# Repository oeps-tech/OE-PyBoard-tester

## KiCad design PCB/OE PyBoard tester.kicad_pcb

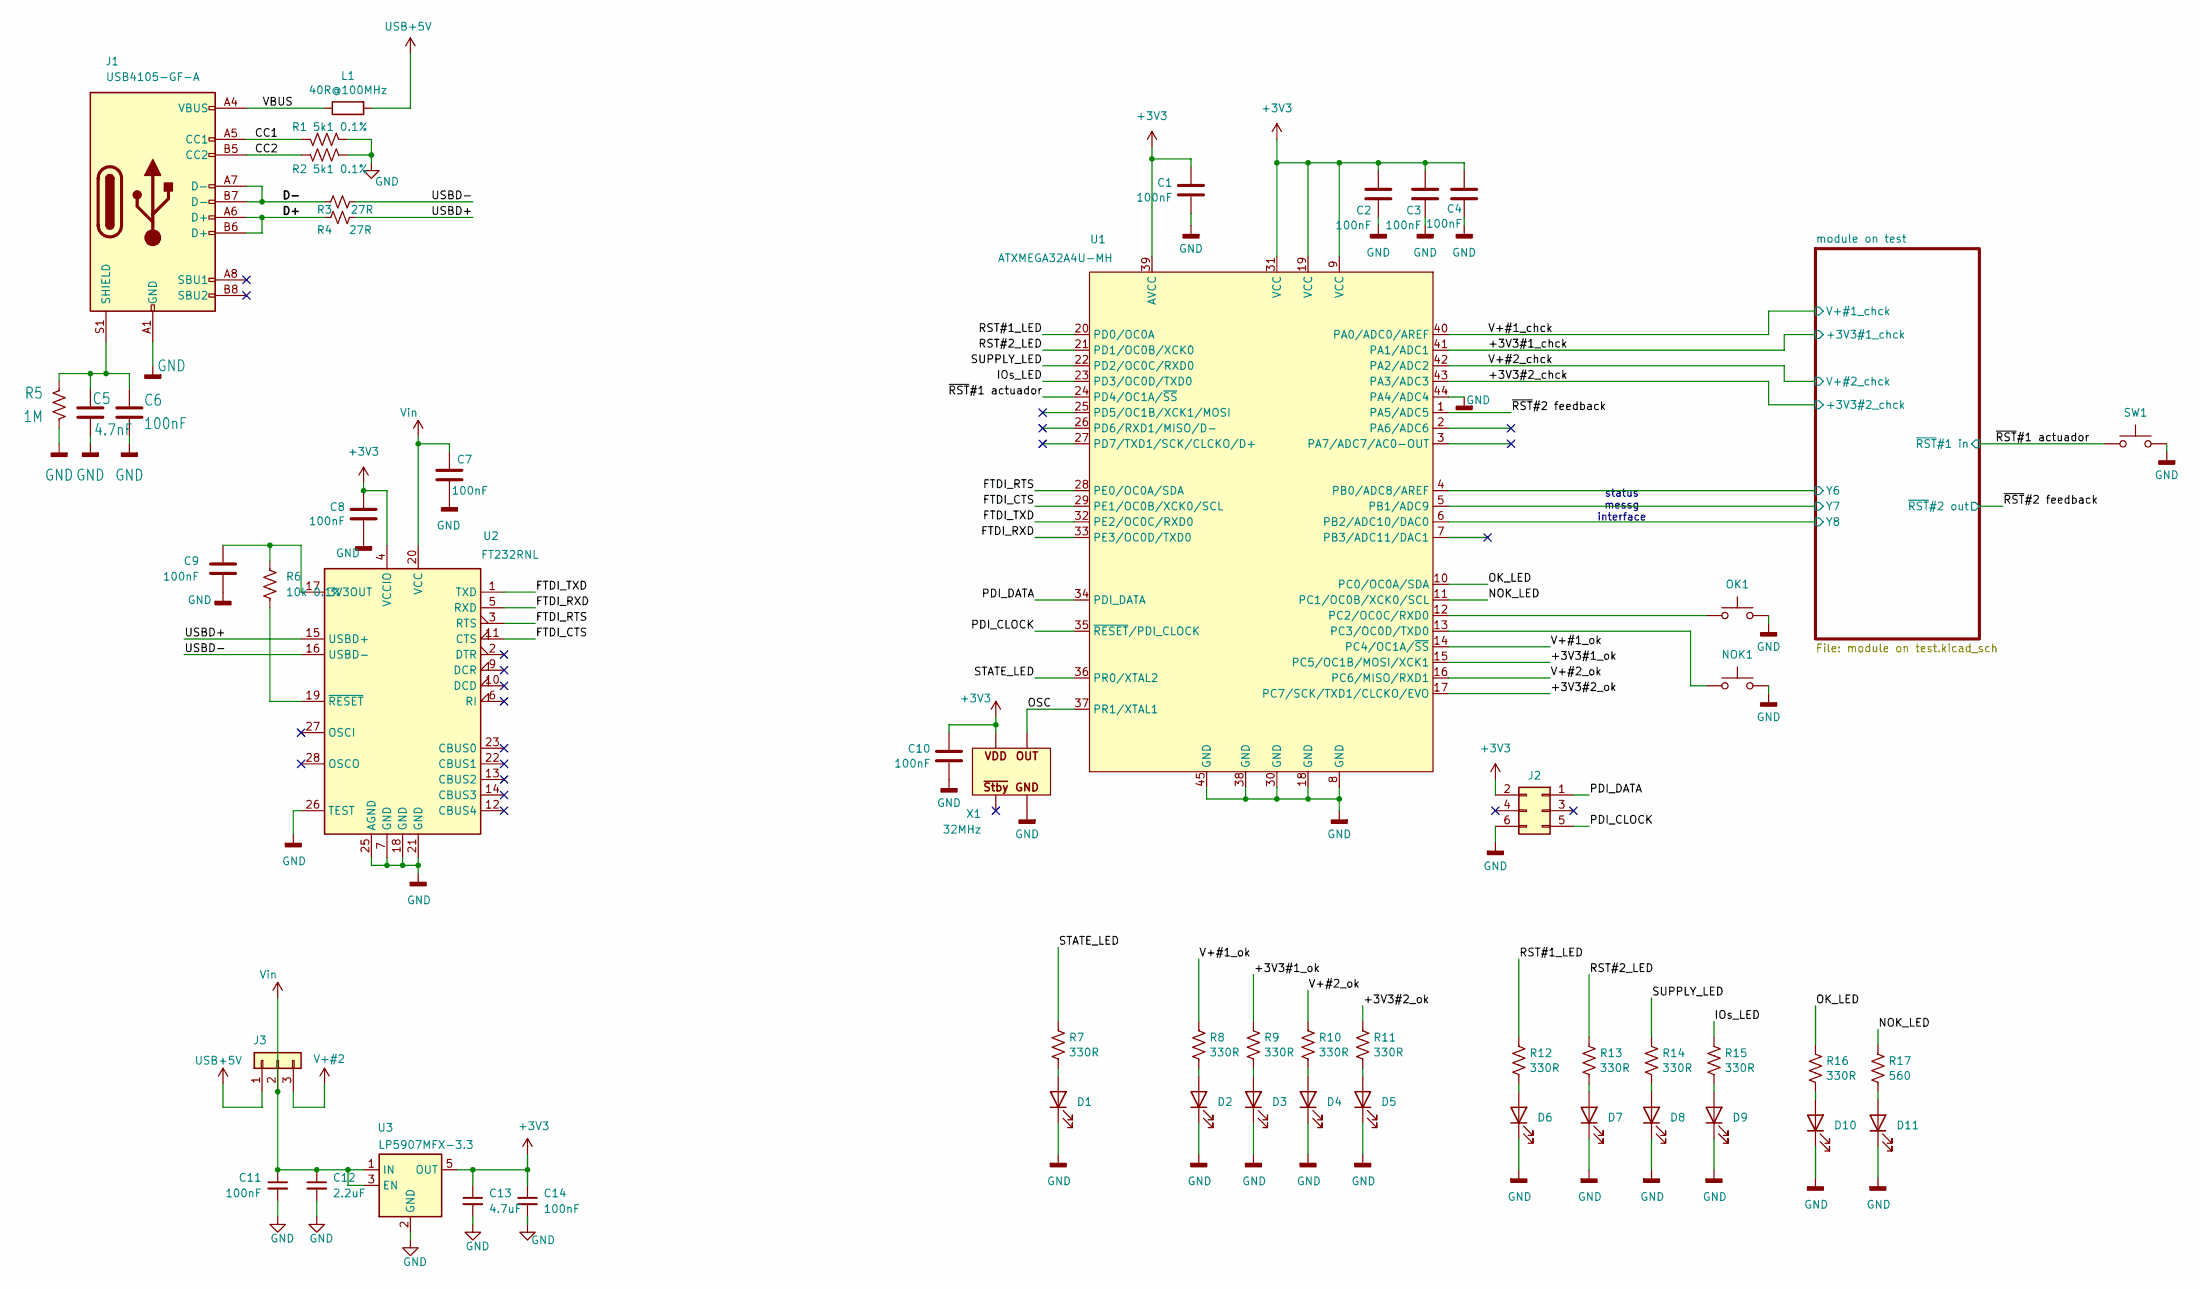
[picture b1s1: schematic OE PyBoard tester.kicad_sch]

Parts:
C1, C2, C3, C4, C6, C7, C8, C9, C10, C11, C14: 100nF; C_0402_1005Metric; MPN CGA2B3X7R1H104K050BB
C5: 4.7nF; C_0402_1005Metric; MPN 885012205084
C12: 2.2uF; C_0603_1608Metric; MPN GRM188R61E225KA12D
C13: 4.7uF; C_0603_1608Metric; MPN C1608X6S1C475K080AC
D1, D2, D3, D4, D5, D6, D7, D8, D9, D10: Green LED; LED_0603_1608Metric; MPN LTST-C191KGKT
D11: Red LED; LED_0603_1608Metric; MPN 5990010007F
J1: USB4105-GF-A; USB_C_Receptacle_GCT_USB4105-xx-A_16P_TopMnt_Horizontal; MPN USB4105-GF-A
J2: 6pin_hd; PinHeader_2x03_P2.54mm_Vertical; MPN 67996-206HLF
J3: 3pin_hd; SolderJumper-3_P1.3mm_Bridged12_RoundedPad1.0x1.5mm; MPN n.a.
L1: 40R@100MHz; R_0805_2012Metric; MPN MI0805K400R-10
NOK1: SW_SPST; SW_SPST_TL3305B; MPN TL3305BF260QG
OK1: SW_SPST; SW_SPST_TL3305B; MPN TL3305BF260QG
R1, R2: 5k1 0.1%; R_0402_1005Metric; MPN RT0402BRD075K1L
R3, R4: 27R; R_0402_1005Metric; MPN RMCF0402FT27R0
R5: 1M; R_0402_1005Metric; MPN CRCW04021M00FKED
R6: 10k 0.1%; R_0402_1005Metric; MPN CPF0402B10KE1
R7, R8, R9, R10, R11, R12, R13, R14, R15, R16: 330R; R_0402_1005Metric; MPN CRCW0402330RFKEDHP
R17: 560; R_0402_1005Metric; MPN CRCW0402560RFKED
SW1: SW_SPST; SW_SPST_TL3305B; MPN TL3305BF260QG
U1: ATXMEGA32A4U-MH; QFN-44-1EP_7x7mm_P0.5mm_EP5.2x5.2mm; MPN ATXMEGA32A4U-MHR
U2: FT232RNL; SSOP-28_5.3x10.2mm_P0.65mm; MPN FT232RNL-REEL
U3: LP5907MFX-3.3; SOT-23-5; MPN LP5907MFX-3.3/NOPB
X1: 32MHz; OSC; MPN DSC1001CI5-032.0000

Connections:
+3V3: C1.1, C2.1, C3.1, C4.1, C8.1, C10.1, C13.1, C14.1, J2.2, U1.9 (VCC), U1.19 (VCC), U1.31 (VCC), U1.39 (AVCC), U2.4 (VCCIO), U3.5 (OUT), X1.4 (VDD); also elsewhere on the board
/+3V3#1_chck: U1.41 (PA1/ADC1); also elsewhere on the board
/+3V3#1_ok: R9.2, U1.15 (PC5/OC1B/MOSI/XCK1)
/+3V3#2_chck: U1.43 (PA3/ADC3); also elsewhere on the board
/+3V3#2_ok: R11.2, U1.17 (PC7/SCK/TXD1/CLCKO/EVO)
/CC1: J1.A5 (CC1), R1.1
/CC2: J1.B5 (CC2), R2.1
/D+: J1.A6 (D+), J1.B6 (D+), R4.2
/D-: J1.A7 (D-), J1.B7 (D-), R3.2
/FTDI_CTS: U1.29 (PE1/OC0B/XCK0/SCL), U2.11 (CTS)
/FTDI_RTS: U1.28 (PE0/OC0A/SDA), U2.3 (RTS)
/FTDI_RXD: U1.33 (PE3/OC0D/TXD0), U2.5 (RXD)
/FTDI_TXD: U1.32 (PE2/OC0C/RXD0), U2.1 (TXD)
/IOs_LED: R15.2, U1.23 (PD3/OC0D/TXD0)
/NOK_LED: R17.2, U1.11 (PC1/OC0B/XCK0/SCL)
/OK_LED: R16.2, U1.10 (PC0/OC0A/SDA)
/OSC: U1.37 (PR1/XTAL1), X1.3 (OUT)
/PDI_CLOCK: J2.5, U1.35 (~RESET/PDI_CLOCK)
/PDI_DATA: J2.1, U1.34 (PDI_DATA)
/RST#1_LED: R12.2, U1.20 (PD0/OC0A)
/RST#2_LED: R13.2, U1.21 (PD1/OC0B/XCK0)
/STATE_LED: R7.2, U1.36 (PR0/XTAL2)
/SUPPLY_LED: R14.2, U1.22 (PD2/OC0C/RXD0)
/USBD+: R4.1, U2.15 (USBD+)
/USBD-: R3.1, U2.16 (USBD-)
/V+#1_chck: U1.40 (PA0/ADC0/AREF); also elsewhere on the board
/V+#1_ok: R8.2, U1.14 (PC4/OC1A/~SS)
/V+#2_chck: U1.42 (PA2/ADC2); also elsewhere on the board
/V+#2_ok: R10.2, U1.16 (PC6/MISO/RXD1)
/VBUS: J1.A4 (VBUS), J1.A9 (VBUS), J1.B4 (VBUS), J1.B9 (VBUS), L1.1
/module on test/PB10-Y9: U1.5 (PB1/ADC9); also elsewhere on the board
/module on test/PB11-Y10: U1.6 (PB2/ADC10/DAC0); also elsewhere on the board
/module on test/PB13-Y6: U1.4 (PB0/ADC8/AREF); also elsewhere on the board
/~RST#1 actuador: SW1.1, U1.24 (PD4/OC1A/~SS); also elsewhere on the board
/~RST#2 feedback: U1.1 (PA5/ADC5); also elsewhere on the board
GND: C1.2, C2.2, C3.2, C4.2, C5.2, C6.1, C7.2, C8.2, C9.1, C10.2, C11.2, C12.2, C13.2, C14.2, D1.1 (K), D2.1 (K), D3.1 (K), D4.1 (K), D5.1 (K), D6.1 (K), D7.1 (K), D8.1 (K), D9.1 (K), D10.1 (K), D11.1 (K), J1.A1 (GND), J1.A12 (GND), J1.B1 (GND), J1.B12 (GND), J2.6, NOK1.2, OK1.2, R1.2, R2.2, R5.1, SW1.2, U1.8 (GND), U1.18 (GND), U1.30 (GND), U1.38 (GND), U1.44 (PA4/ADC4), U1.45 (GND), U2.7 (GND), U2.18 (GND), U2.21 (GND), U2.25 (AGND), U2.26 (TEST), U3.2 (GND), X1.2 (GND); also elsewhere on the board
unnamed: D1.2 (A), R7.1
unnamed: D2.2 (A), R8.1
unnamed: D3.2 (A), R9.1
unnamed: D4.2 (A), R10.1
unnamed: D5.2 (A), R11.1
unnamed: D6.2 (A), R12.1
unnamed: D7.2 (A), R13.1
unnamed: D8.2 (A), R14.1
unnamed: D9.2 (A), R15.1
unnamed: D10.2 (A), R16.1
unnamed: D11.2 (A), R17.1
unnamed: C5.1, C6.2, J1.S1 (SHIELD), R5.2
unnamed: OK1.1, U1.12 (PC2/OC0C/RXD0)
unnamed: NOK1.1, U1.13 (PC3/OC0D/TXD0)
unnamed: C9.2, R6.1, U2.17 (3V3OUT)
unnamed: R6.2, U2.19 (~RESET)
USB+5V: J3.1, L1.2
V+#2: J3.3; also elsewhere on the board
Vin: C7.1, C11.1, C12.1, J3.2, U2.20 (VCC), U3.1 (IN), U3.3 (EN)

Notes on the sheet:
status messg interface

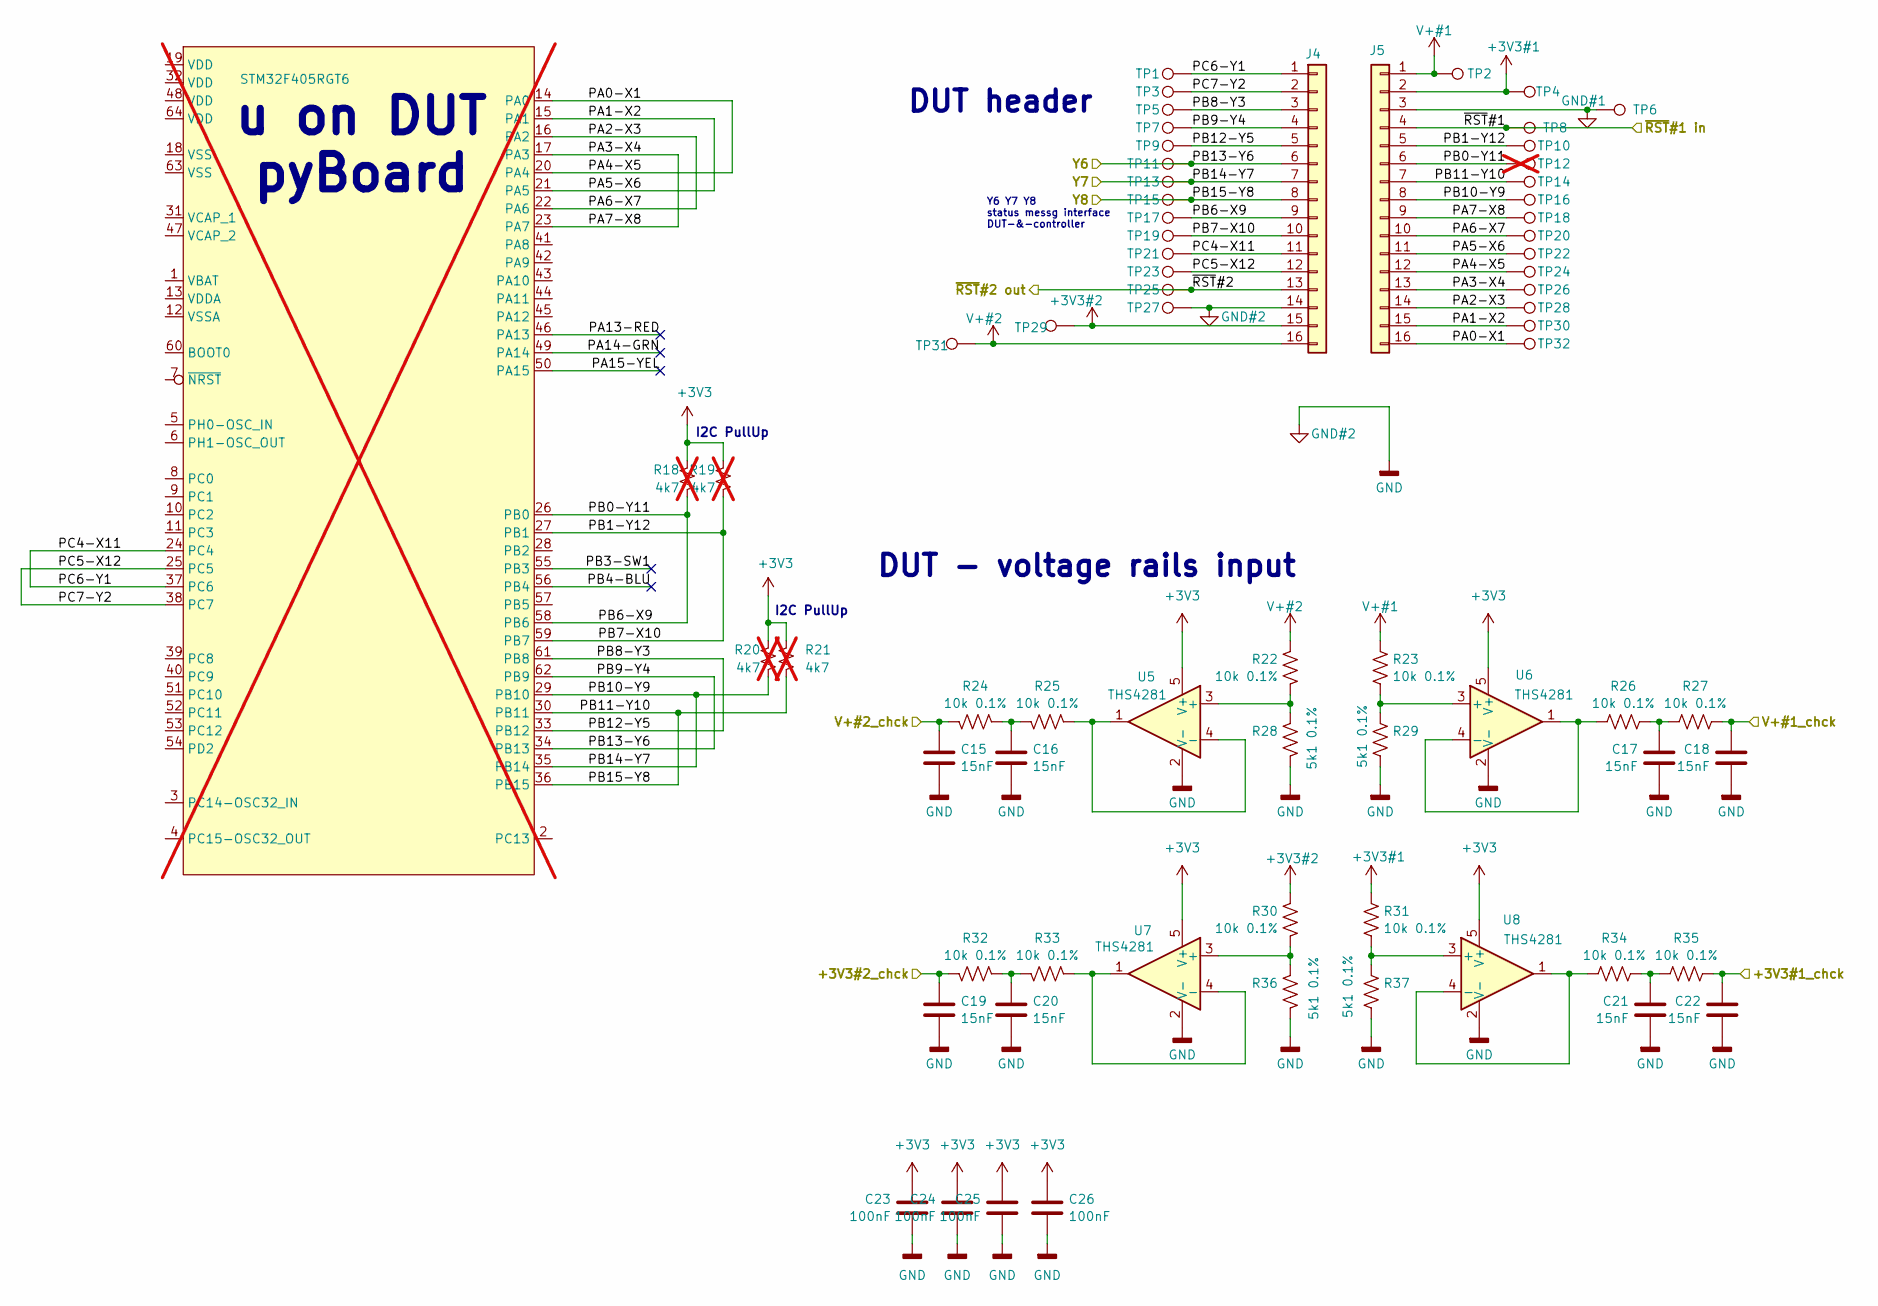
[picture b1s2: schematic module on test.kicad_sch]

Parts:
C15, C16, C17, C18, C19, C20, C21, C22: 15nF; C_0402_1005Metric_Pad0.74x0.62mm_HandSolder; MPN CGA2B3X7R1V153K050BB
C23, C24, C25, C26: 100nF; C_0402_1005Metric; MPN CGA2B3X7R1H104K050BB
J4, J5: Conn_01x08; PinHeader_1x16_P2.54mm_Vertical; MPN TSW-116-06-T-S
R18, R19, R20, R21: 4k7; R_0402_1005Metric; MPN ERJ-2RKF4701X; not fitted
R22, R23, R24, R25, R26, R27, R30, R31, R32, R33, R34, R35: 10k 0.1%; R_0402_1005Metric; MPN CPF0402B10KE1
R28, R29, R36, R37: 5k1 0.1%; R_0402_1005Metric; MPN RT0402BRD075K1L
TP1, TP2, TP3, TP4, TP5, TP7, TP8, TP9, TP10, TP11, TP13, TP14, TP15, TP16, TP17, TP18, TP19, TP20, TP21, TP22, TP23, TP24, TP25, TP26, TP28, TP29, TP30, TP31, TP32: TestPoint; TestPoint_Keystone_5015_Micro_Mini
TP6, TP27: TestPoint; TestPoint_Keystone_5000-5004_Miniature
TP12: TestPoint; TestPoint_Keystone_5015_Micro_Mini; not fitted
U4: STM32F405RGT6; LQFP-64_10x10mm_P0.5mm; MPN STM32F405RGT6; not fitted
U5, U6, U7, U8: THS4281; SOT-23-5; MPN THS4281DBVT

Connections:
+3V3: C23.1, C24.1, C25.1, C26.1, R18.1, R19.1, R20.1, R21.1, U5.5 (V+), U6.5 (V+), U7.5 (V+), U8.5 (V+); also elsewhere on the board
+3V3#1: J5.2, R31.2, TP4.1
+3V3#2: J4.15, R30.2, TP29.1
/+3V3#1_chck: C22.1, R35.2; also elsewhere on the board
/+3V3#2_chck: C19.1, R32.2; also elsewhere on the board
/V+#1_chck: C18.1, R27.2; also elsewhere on the board
/V+#2_chck: C15.1, R24.2; also elsewhere on the board
/module on test/PA0-X1: J5.12, J5.16, TP24.1, TP32.1, U4.14 (PA0), U4.20 (PA4)
/module on test/PA1-X2: J5.11, J5.15, TP22.1, TP30.1, U4.15 (PA1), U4.21 (PA5)
/module on test/PA2-X3: J5.10, J5.14, TP20.1, TP28.1, U4.16 (PA2), U4.22 (PA6)
/module on test/PA3-X4: J5.9, J5.13, TP18.1, TP26.1, U4.17 (PA3), U4.23 (PA7)
/module on test/PB0-Y11: J4.9, J5.6, R18.2, TP12.1, TP17.1, U4.26 (PB0), U4.58 (PB6)
/module on test/PB1-Y12: J4.10, J5.5, R19.2, TP10.1, TP19.1, U4.27 (PB1), U4.59 (PB7)
/module on test/PB10-Y9: J4.7, J5.8, R20.2, TP13.1, TP16.1, U4.29 (PB10), U4.35 (PB14); also elsewhere on the board
/module on test/PB11-Y10: J4.8, J5.7, R21.2, TP14.1, TP15.1, U4.30 (PB11), U4.36 (PB15); also elsewhere on the board
/module on test/PB12-Y5: J4.3, J4.5, TP5.1, TP9.1, U4.33 (PB12), U4.61 (PB8)
/module on test/PB13-Y6: J4.4, J4.6, TP7.1, TP11.1, U4.34 (PB13), U4.62 (PB9); also elsewhere on the board
/module on test/PC4-X11: J4.1, J4.11, TP1.1, TP21.1, U4.24 (PC4), U4.37 (PC6)
/module on test/PC5-X12: J4.2, J4.12, TP3.1, TP23.1, U4.25 (PC5), U4.38 (PC7)
/~RST#1 actuador: J5.4, TP8.1; also elsewhere on the board
/~RST#2 feedback: J4.13, TP25.1; also elsewhere on the board
GND: C15.2, C16.2, C17.2, C18.2, C19.2, C20.2, C21.2, C22.2, C23.2, C24.2, C25.2, C26.2, J4.14, R28.1, R29.1, R36.1, R37.1, TP27.1, U5.2 (V-), U6.2 (V-), U7.2 (V-), U8.2 (V-); also elsewhere on the board
GND#1: J5.3, TP6.1
unnamed: C16.1, R24.1, R25.2
unnamed: C17.1, R26.2, R27.1
unnamed: C20.1, R32.1, R33.2
unnamed: C21.1, R34.2, R35.1
unnamed: R22.1, R28.2, U5.3 (+)
unnamed: R25.1, U5.1, U5.4 (-)
unnamed: R23.1, R29.2, U6.3 (+)
unnamed: R26.1, U6.1, U6.4 (-)
unnamed: R30.1, R36.2, U7.3 (+)
unnamed: R33.1, U7.1, U7.4 (-)
unnamed: R31.1, R37.2, U8.3 (+)
unnamed: R34.1, U8.1, U8.4 (-)
V+#1: J5.1, R23.2, TP2.1
V+#2: J4.16, R22.2, TP31.1; also elsewhere on the board

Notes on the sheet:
DUT header
I2C PullUp
DUT - voltage rails input
Y6 Y7 Y8 status messg interface DUT-&-controller
u on DUT pyBoard

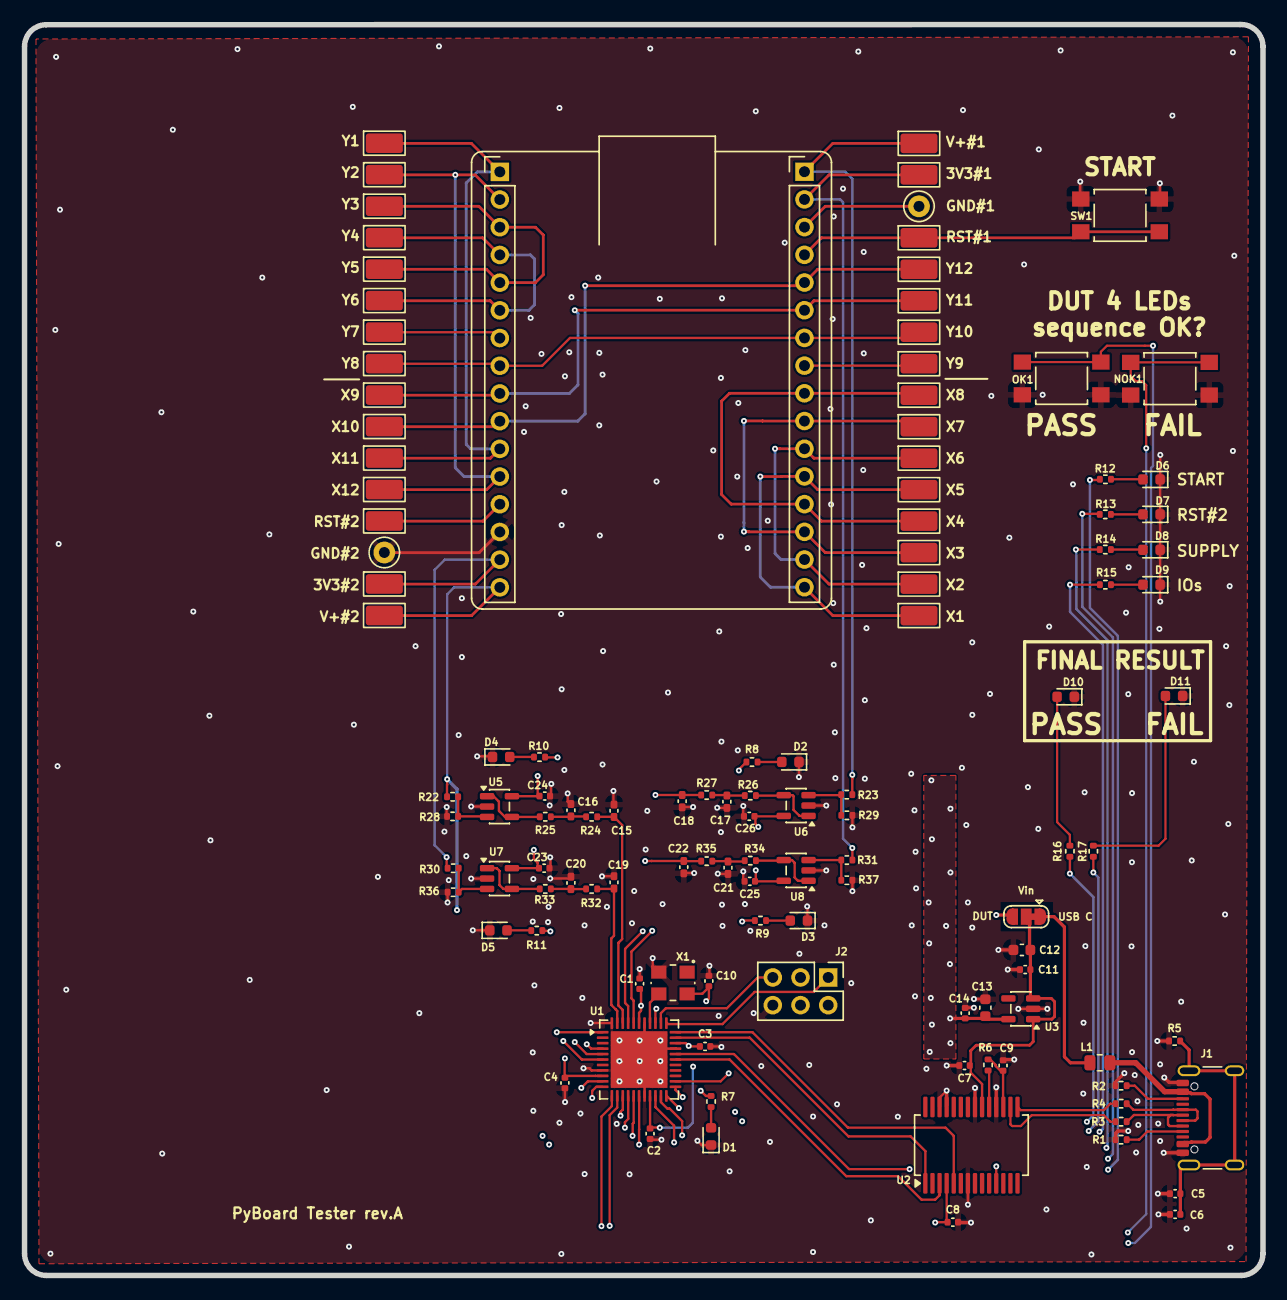
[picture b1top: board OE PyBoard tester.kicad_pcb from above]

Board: 4 copper layers, 113.5 x 114.7 mm, 119 parts (0 on the bottom side), 80 nets.

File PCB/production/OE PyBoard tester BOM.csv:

#;Reference;Qty;Value;Footprint;DNP;OEPSPN;Description;MPN
1;C5;1;4.7nF;Capacitor_SMD:C_0402_1005Metric;;OEPS010017;Unpolarized capacitor, small symbol;885012205084
2;C12;1;2.2uF;Capacitor_SMD:C_0603_1608Metric;;OEPS010075;Unpolarized capacitor, small symbol;GRM188R61E225KA12D
3;C13;1;4.7uF;Capacitor_SMD:C_0603_1608Metric;;OEPS010018;Unpolarized capacitor, small symbol;C1608X6S1C475K080AC
4;C1,C2,C3,C4,C6,C7,C8,C9,C10,C11,C14,C23,C24,C25,C26;15;100nF;Capacitor_SMD:C_0402_1005Metric;;OEPS010016;SMD CER 0402 100nF 50V ±10% X7R;CGA2B3X7R1H104K050BB
5;C15,C16,C17,C18,C19,C20,C21,C22;8;15nF;Capacitor_SMD:C_0402_1005Metric_Pad0.74x0.62mm_HandSolder;;OEPS010023;SMD CER 0402 15nF 35V ±10% X7R;CGA2B3X7R1V153K050BB
6;D11;1;Red LED;LED_SMD:LED_0603_1608Metric;;OEPS030044;LED 0603 Red 633nm 20mA;5990010007F
7;D1,D2,D3,D4,D5,D6,D7,D8,D9,D10;10;Green LED;LED_SMD:LED_0603_1608Metric;;OEPS030005 ;LED 0603 Green 571nm 20mA,Light emitting diode;LTST-C191KGKT
8;J1;1;USB4105-GF-A;PyBoardTester FootprintLib:USB_C_Receptacle_GCT_USB4105-xx-A_16P_TopMnt_Horizontal;;OEPS070105;USB 2.0-only 16P Type-C Receptacle connector;USB4105-GF-A
9;J2;1;6pin_hd;Connector_PinHeader_2.54mm:PinHeader_2x03_P2.54mm_Vertical;;OEPS070015;HEADER 2.54MM straight 2x3POS;67996-206HLF
10;J4,J5;2;Conn_01x08;Connector_PinHeader_2.54mm:PinHeader_1x16_P2.54mm_Vertical;;OEPS070109;HEADER VERT 16POS 2.54MM;TSW-116-06-T-S
11;L1;1;40R@100MHz;Resistor_SMD:R_0805_2012Metric;;OEPS040003;FERRITE BEAD SMD 40Ω 2A 50mΩ;MI0805K400R-10
12;NOK1,OK1,SW1;3;SW_SPST;Button_Switch_SMD:SW_SPST_TL3305B;;OEPS100061;Push button switch;TL3305BF260QG
13;R5;1;1M;Resistor_SMD:R_0402_1005Metric;;OEPS020026;SMD 0402 1MΩ ±1% 0.063W;CRCW04021M00FKED
14;R17;1;560;Resistor_SMD:R_0402_1005Metric;;OEPS020193;Resistor, small US symbol;CRCW0402560RFKED
15;R1,R2,R28,R29,R36,R37;6;5k1 0.1%;Resistor_SMD:R_0402_1005Metric;;OEPS020203;SMD 0402 5.1kΩ ±0.1% 0.063W;RT0402BRD075K1L
16;R3,R4;2;27R;Resistor_SMD:R_0402_1005Metric;;OEPS020170;Resistor, small US symbol;RMCF0402FT27R0
17;R6,R22,R23,R24,R25,R26,R27,R30,R31,R32,R33,R34,R35;13;10k 0.1%;Resistor_SMD:R_0402_1005Metric;;OEPS020043;SMD 0402 10kΩ ±0.1% 0.063W;CPF0402B10KE1
18;R7,R8,R9,R10,R11,R12,R13,R14,R15,R16;10;330R;Resistor_SMD:R_0402_1005Metric;;OEPS020191;Resistor, small US symbol;CRCW0402330RFKEDHP
19;U1;1;ATXMEGA32A4U-MH;Package_DFN_QFN:QFN-44-1EP_7x7mm_P0.5mm_EP5.2x5.2mm;;OEPS080116;MCU ATXMEGA A4U 8bits 32KB;ATXMEGA32A4U-MHR
20;U2;1;FT232RNL;Package_SO:SSOP-28_5.3x10.2mm_P0.65mm;;OEPS080093;USB Interface IC USB to Serial UART;FT232RNL-REEL
21;U3;1;LP5907MFX-3.3;Package_TO_SOT_SMD:SOT-23-5;;OEPS080016;250-mA Ultra-Low-Noise Low-IQ LDO, 3.3V, SOT-23;LP5907MFX-3.3/NOPB
22;U5,U6,U7,U8;4;THS4281;Package_TO_SOT_SMD:SOT-23-5;;OEPS080038;OPAMP VFB 1 CIRCUIT;THS4281DBVT
23;X1;1;32MHz;PyBoardTester FootprintLib:OSC;;OEPS080018;OSC 32MHz 10ppm;DSC1001CI5-032.0000

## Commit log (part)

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2025-12-09 Added .gitignore for KiCad project files
2026-01-21 Add OE PyBoard tester PCB design files
    Initial commit of the OE PyBoard tester project.
2026-06-10 Add firmware .gitignore and registers.xls
2026-06-10 Add shunts mapping file for DUT firmware
2026-06-10 Move registers.xls to PyBoardTester
    Rename registers.xls from Firmware/AcquisitionTester to Firmware/PyBoardTester (100% identical file). No content changes—just relocating the spreadsheet to reflect directory reorganization.
